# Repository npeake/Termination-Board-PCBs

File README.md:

# Termination-Board-PCBs
This repository contains KiCad PCB designs created by me for the ATLAS ITk Pixel Type-1 Services. These boards will carry high voltage sensor bias, low voltage high current module power, and module communication signals into the ATLAS detector for the ITk Pixel modules.

Termination Boards [v1](https://github.com/npeake/Termination-Board-PCBs/tree/main/Termination%20Board%20v1) and [v2](https://github.com/npeake/Termination-Board-PCBs/tree/main/Termination%20Board%20v2) are preliminary designs which were used for testing and are now outdated.

[Termination Board v3](https://github.com/npeake/Termination-Board-PCBs/tree/main/Termination%20Board%20v3) is the design used for the 19-x prototypes.

[Termination Board DCS v2](https://github.com/npeake/Termination-Board-PCBs/tree/main/Termination%20Board%20DCS%20v2) is an updated version of only the DCS board from the term board v3. This board was used for DCS supply on the 19-x Coupled Ring prototype PP0. It accounts for changes of the PP0 for only the 19-x prototypes, and is not part of the final design termination boards.

[Termination Board v4](https://github.com/npeake/Termination-Board-PCBs/tree/main/Termination%20Board%20v4) includes updated designs to the termination boards to reorrient the Type-1 services landing pads by 45 degrees. This will ease strain on the attached cables and their solder joints compared to an abrupt 90 degree bend.

[19-x Prototype Cable Mapping](https://github.com/npeake/Termination-Board-PCBs/tree/main/19-x%20Prototype%20Cable%20Mapping) directory contains schematics for the Type-1 service cable bundle wiring for the 19-x prototypes. These include prototypes of a Coupled Ring and an L0+2L1 Barrel. These differ from the final design in that the PP1 connectors used are banana jacks, SHV plugs, and DB25 connectors and the L0+2L1 PP0 is divided into 3 seperate PP0's for ease of prototyping and data breakout.

[SCIPP_Connectors](https://github.com/npeake/Termination-Board-PCBs/tree/main/SCIPP_Connectors) in the main repository directory contains all connector footprints designed and used for this project. Some directories contain another copy of SCIPP_Connectors because they rely on earlier versions of the connectors for their designs. However, the main directory connector folder contains the most recently updated footprints along with 3D models.

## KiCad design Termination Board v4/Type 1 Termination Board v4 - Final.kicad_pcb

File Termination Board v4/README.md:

This folder contains final design files for termination boards for the Type-1 services. Type 1 Termination Board v4 Design corresponds to the design process, last version v3 boards for reference, and the multiple designs created for v4. Type 1 Termination Board v4 Final is the final design chosen for termination boards and is complete.

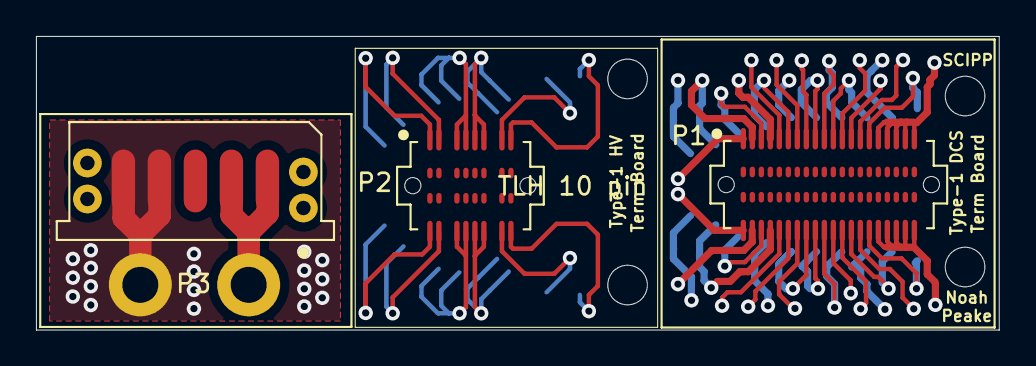
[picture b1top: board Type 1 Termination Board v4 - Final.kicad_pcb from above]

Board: 4 copper layers, 53.5 x 16.3 mm, 9 parts (0 on the bottom side), 6 nets.

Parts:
H1, H1#2, H2, H2#2: MountingHole_2.2mm_M2
J2, J3: Conn_01x01_Female; 14AWG_THT
P1: TLH 20 pin; TLH_20_Pin
P2: TLH 10 pin; 19-1_TLH_HV
P3: UMPS 5 pin; UMPS_5_Pin

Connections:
Gnd: P1.1, P1.2, P1.5, P1.6, P1.9, P1.10, P1.13, P1.14, P1.19, P1.20, P1.23, P1.24, P1.27, P1.28, P1.31, P1.32, P1.33, P1.34, P1.35, P1.36, P1.37, P1.38, P1.39, P1.40, P3.3
HV_Quad_rtn: P2.11, P2.12, P2.13, P2.14
HV_Triplet1: P2.1, P2.2
HV_Triplet_rtn: P2.7, P2.8, P2.9, P2.10
LV: J2.1, P3.1, P3.2
LV_rtn: J3.1, P3.4, P3.5

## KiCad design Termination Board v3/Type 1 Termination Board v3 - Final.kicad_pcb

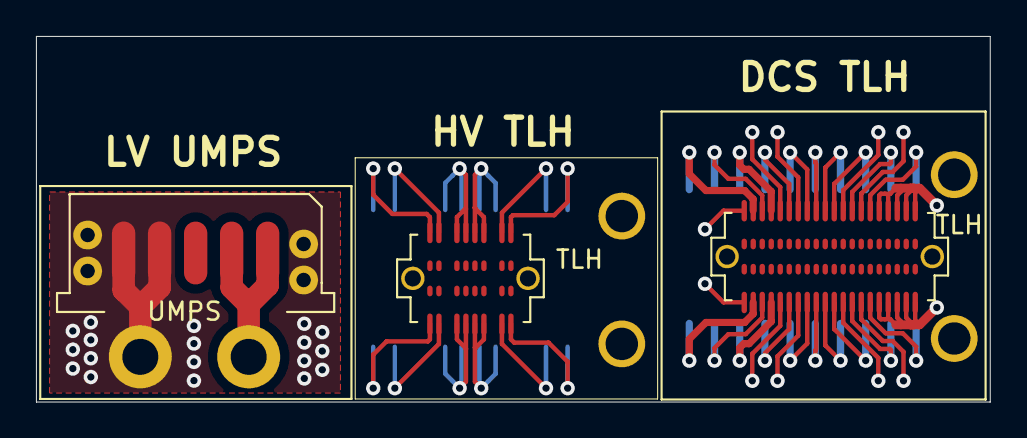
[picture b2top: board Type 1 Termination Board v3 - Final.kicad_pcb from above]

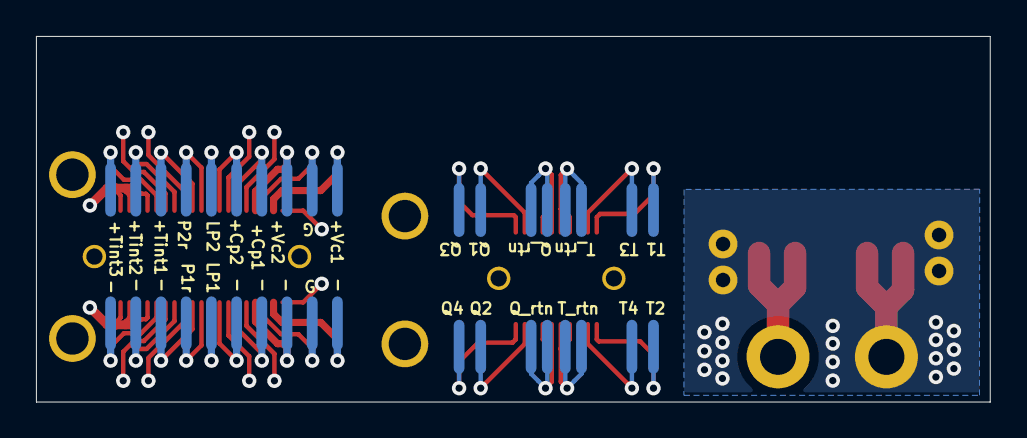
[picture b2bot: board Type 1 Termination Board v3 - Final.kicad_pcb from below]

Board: 4 copper layers, 53.0 x 20.3 mm, 13 parts (4 on the bottom side), 3 nets.

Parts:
J2, J3: Conn_01x01_Female; 14AWG_THT
J10: UMPS; UMPS 5 Pin
J11: TLH; 19-1_TLH_HV
J12: TLH; TLH 20 Pin
J20, J21, J22, J23: PEEK_screw
P1, P2, P3, P4: Pad_Array_2

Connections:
/LV: J2.1, J10.1, J10.2
/return: J3.1, J10.4, J10.5, J10.6, J10.7, J10.8, J10.9
GND: J10.3, J12.1, J12.2, J12.5, J12.6, J12.9, J12.10, J12.13, J12.14, J12.19, J12.20, J12.23, J12.24, J12.27, J12.28, J12.31, J12.32, J12.33, J12.34, J12.35, J12.36, J12.37, J12.38, J12.39, J12.40, J12.41, J12.42, J22.43, J23.44, P1.6, P1.20, P2.5, P2.19

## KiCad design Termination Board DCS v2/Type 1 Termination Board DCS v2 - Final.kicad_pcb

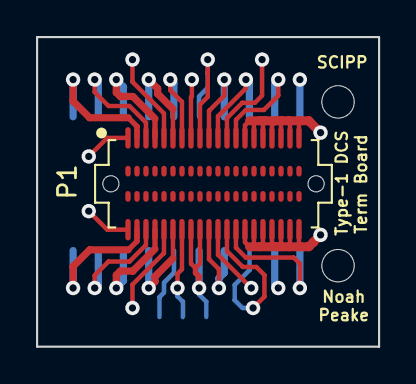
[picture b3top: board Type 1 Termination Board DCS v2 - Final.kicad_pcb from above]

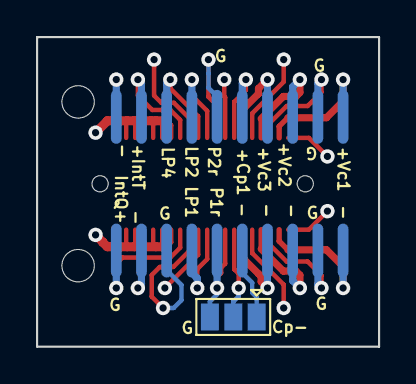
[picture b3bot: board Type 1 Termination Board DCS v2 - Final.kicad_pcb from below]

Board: 4 copper layers, 19.0 x 17.2 mm, 5 parts (2 on the bottom side), 16 nets.

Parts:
J22, J23: PEEK_screw
P1: TLH 20 Pin; TLH_20_Pin
P1#2, P2: Pad_Array_2

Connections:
Can_pwr1: P1.13, P2.13
Can_pwr1-: P1.14, P1#2.14
Gnd: P1.1, P1.2, P1.5, P1.6, P1.9, P1.10, P1.16, P1.17, P1.18, P1.23, P1.24, P1.27, P1.28, P1.29, P1.30, P1.31, P1.32, P1.33, P1.34, P1.35, P1.36, P1.37, P1.38, P1.39, P1.40, P1#2.6, P1#2.16, P1#2.24, P2.5, P2.17
Interlock_Q+: P1.26, P1#2.26
Interlock_Q-: P1.15, P1#2.15
Interlock_T+: P1.25, P2.25
Interlock_T-: P1.22, P2.22
LP_mode1: P1.20, P1#2.20
LP_mode2: P1.19, P2.19
LP_mode4: P1.21, P2.21
Vcan1+: P1.3, P2.3
Vcan1-: P1.4, P1#2.4
Vcan2+: P1.7, P2.7
Vcan2-: P1.8, P1#2.8
Vcan3+: P1.11, P2.11
Vcan3-: P1.12, P1#2.12
